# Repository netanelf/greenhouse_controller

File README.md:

# greenhouse_controller

## Executive Summary

An edge-based IoT monitoring and irrigation control system designed for long-term autonomous operation. 
The system integrates custom hardware (Raspberry Pi HAT), environmental sensors, actuator control (relays/SSR), event-driven automation logic, 
and a web-based monitoring interface built with Django. 
Deployed in real-world conditions and operated continuously for multiple years, enabling reliable unattended autonomous operation.

## Introduction

This project was developed to explore the design of reliable edge-based automation systems combining custom hardware, embedded software, and a full-stack web interface. The system was deployed in a real greenhouse environment and operated continuously over multiple growing seasons.

## System Architecture

The system follows an edge-controller architecture:

Sensors → Custom HAT Board → Raspberry Pi (Edge Controller) → Django Backend → Web Interface

- Local sensing and actuation handled directly by the Raspberry Pi.
- Control logic executed locally (no cloud dependency).
- Web interface for monitoring, configuration, and manual override.
- SQLite-based data storage with lightweight retention strategy.
- Event-driven automation engine enables flexible rule-based control without modifying core application code.

## Key Engineering Decisions

- Used 74HC595 shift register to expand GPIO outputs efficiently.
- Designed custom PCB HAT for reliable sensor and actuator interfacing.
- Implemented database separation strategy to mitigate SD-card wear and improve long-term reliability.
- Implemented event-condition-action flow engine for flexible automation logic.
- Ensured safe driving of relays via transistor stages and current-limited LED indicators.

## Hardware & Sensor Integration Overview

The system interfaces with temperature, humidity, light, and water flow sensors, as well as relay-controlled irrigation outputs and a camera module for periodic image capture.

The custom HAT board provides electrical interfacing, signal conditioning, and output expansion.

The architecture was designed to run on a Raspberry Pi, using its IOs through a dedicated hat board that interfaces directly with sensors and relays.
Key hardware features:
1. A 74HC595A shift register was used to expand available digital outputs.
2. the board includes:
   1. Connector for external 5V power capable of supplying the board and/or the HAT (selectable via solder jumper)
   2. 4 outputs that can control a SSR/ Relay with connectors for an indicator LED (board includes a current limiting resistor)
   3. 4 outputs of raw digital pins from the shift register (no LED/ Driver/ protection)
   4. 4 connectors for I2C sensors, connectors include the communication pins (scl,sda) and a 3.3/4V supply selected with a soldered jumper
   5. 3 dedicated connectors for a "Maxim Integrated DS18B20" 1-wire thermometer
   6. 3 dedicated connectors for a "AM2302/DHT22" digital temperature and humidity sensor
   7. pins for interfacing with all the RPi GPIOs (40p connector)
   8. pads for the shift register, driving transistors, and passive components

The project was built using the Django python library that implements the backend and frontend.
Custom drivers were implemented where required; existing open-source drivers were integrated where appropriate.
for example:
1. Maxim Integrated DS18B20 thermometer
2. AM2302/DHT22 temperature and humidity sensor
3. generic water flow sensor (pulse per known amount of flow)
4. TSL2561 Lux sensor
5. generic digital input/output lines (can be used for level sensors etc.)
6. a camera driver (uses the RPi camera interface)
   
## hat board schematic and layout

## Control options

The system implements an event-condition-action automation model. 
Users can define scheduled events, conditional logic, and associated control actions through the web interface.

an example watering flow can be:
- at 8:00 of days 1,3,5:
	- turn ON relay A
	- wait 10 minutes
	- turn OFF relay A

another flow can be to save sensor images to a DB:
- every 5 minutes:
  - read sensor A, save value to DB
  - read sensor B, save value to DB
  - ...
 
## web UI

The Django-based web interface provides:

- Configuration of automation flows
- Real-time visualization of sensor data
- Current relay states and actuator status
- Latest captured camera image
- Manual override controls for direct actuation

The Django admin interface is used for advanced configuration and rule management.

## Lessons Learned

### Edge System Constraints
- SD-card wear and limited I/O throughput require careful database management.
	- Measurements exceeding a configured retention threshold are migrated from db.sqlite3 to backup.sqlite3 to limit database growth and reduce SD-card wear.
 	- backup.sqlite3 can be copied regularly to a strong computer
- Power stability is critical when driving inductive loads.

### System Design Insight
- Designing for maintainability and observability from the beginning significantly simplifies long-term operation and troubleshooting.

### Reliability
- Long-running systems require watchdog-like recovery strategies.
- Sensor drift and environmental exposure must be handled in software logic.

### Hardware–Software Integration
- Clear abstraction layers between hardware drivers and application logic simplify long-term maintenance.

## Potential Extensions
- Cloud integration for remote monitoring
- OTA update mechanism
- Containerized deployment model
- Centralized logging and metrics collection

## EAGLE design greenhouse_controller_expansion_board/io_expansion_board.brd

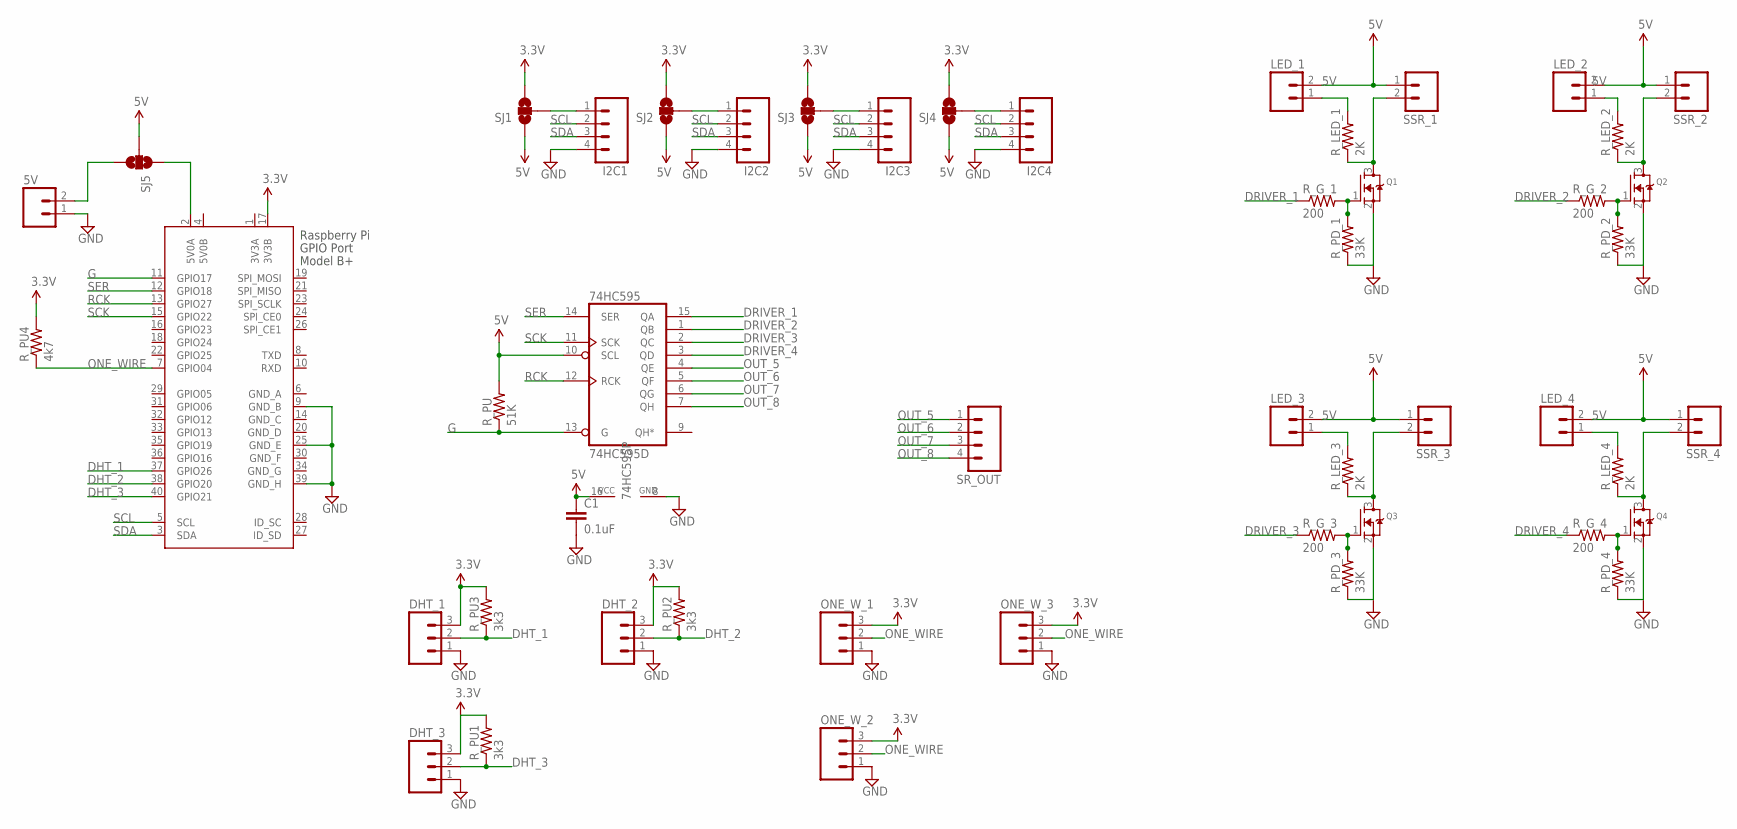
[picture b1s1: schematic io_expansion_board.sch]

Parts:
5V: M023.5MM; SCREWTERMINAL-3.5MM-2
74HC595: 74HC595D; SO16
C1: 0.1uF; 0603-CAP
DHT_1, DHT_2, DHT_3: M03POLAR; MOLEX-1X3
I2C1, I2C2, I2C3, I2C4: M04PTH; 1X04
LED_1, LED_2, LED_3, LED_4: M02PTH; 1X02
ONE_W_1, ONE_W_2, ONE_W_3: M03POLAR; MOLEX-1X3
Q1, Q2, Q3, Q4: MOSFET-NREFLOW; SOT23
R_G_1, R_G_2, R_G_3, R_G_4: 200; 0603-RES
R_LED_1, R_LED_2, R_LED_3, R_LED_4: 2K; 0603-RES
R_PD_1, R_PD_2, R_PD_3, R_PD_4: 33K; 0603-RES
R_PU: 51K; 0603-RES
R_PU1, R_PU2, R_PU3: 3k3; 0603-RES
R_PU4: 4k7; 0603-RES
SJ1, SJ2, SJ3, SJ4, SJ5: SOLDERJUMPER_2WAYS; SJ_3
SR_OUT: M04PTH; 1X04
SSR_1, SSR_2, SSR_3, SSR_4: M02PTH; 1X02
X2: RASPI_BOARD_B+#_HDC; RASPI_BOARD_B+HAT_DF_CF

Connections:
3.3V: DHT_1.3, DHT_2.3, DHT_3.3, ONE_W_1.3, ONE_W_2.3, ONE_W_3.3, R_PU1.2, R_PU2.2, R_PU3.2, R_PU4.2, SJ1.3, SJ2.3, SJ3.3, SJ4.3, X2.17 (3V3B)
3V3A: X2.1 (3V3A)
5V: 74HC595.10 (SCL), 74HC595.16 (VCC), C1.1, LED_1.2, LED_2.2, LED_3.2, LED_4.2, R_PU.2, SJ1.1, SJ2.1, SJ3.1, SJ4.1, SJ5.2, SSR_1.1, SSR_2.1, SSR_3.1, SSR_4.1
5V0B: X2.4 (5V0B)
DHT_1: DHT_1.2, R_PU3.1, X2.37 (GPIO26)
DHT_2: DHT_2.2, R_PU2.1, X2.38 (GPIO20)
DHT_3: DHT_3.2, R_PU1.1, X2.40 (GPIO21)
DRIVER_1: 74HC595.15 (QA), R_G_1.1
DRIVER_2: 74HC595.1 (QB), R_G_2.1
DRIVER_3: 74HC595.2 (QC), R_G_3.1
DRIVER_4: 74HC595.3 (QD), R_G_4.1
G: 74HC595.13 (G), R_PU.1, X2.11 (GPIO17)
GND: 5V.1, 74HC595.8 (GND), C1.2, DHT_1.1, DHT_2.1, DHT_3.1, I2C1.4 (GND), I2C2.4 (GND), I2C3.4 (GND), I2C4.4 (GND), ONE_W_1.1, ONE_W_2.1, ONE_W_3.1, Q1.2 (S), Q2.2 (S), Q3.2 (S), Q4.2 (S), R_PD_1.1, R_PD_2.1, R_PD_3.1, R_PD_4.1, X2.9 (GND_B), X2.25 (GND_E), X2.39 (GND_H)
GND_A: X2.6 (GND_A)
GND_C: X2.14 (GND_C)
GND_D: X2.20 (GND_D)
GND_F: X2.30 (GND_F)
GND_G: X2.34 (GND_G)
unnamed: Q2.1 (G), R_G_2.2, R_PD_2.2
unnamed: Q2.3 (D), R_LED_2.1, SSR_2.2
unnamed: LED_2.1, R_LED_2.2
unnamed: Q3.1 (G), R_G_3.2, R_PD_3.2
unnamed: Q1.1 (G), R_G_1.2, R_PD_1.2
unnamed: Q1.3 (D), R_LED_1.1, SSR_1.2
unnamed: LED_1.1, R_LED_1.2
unnamed: Q3.3 (D), R_LED_3.1, SSR_3.2
unnamed: LED_3.1, R_LED_3.2
unnamed: Q4.1 (G), R_G_4.2, R_PD_4.2
unnamed: Q4.3 (D), R_LED_4.1, SSR_4.2
unnamed: LED_4.1, R_LED_4.2
unnamed: I2C1.1 (SCL), SJ1.2
unnamed: I2C2.1 (SCL), SJ2.2
unnamed: I2C3.1 (SCL), SJ3.2
unnamed: I2C4.1 (SCL), SJ4.2
unnamed: SJ5.1, X2.2 (5V0A)
unnamed: 5V.2, SJ5.3
ONE_WIRE: ONE_W_1.2, ONE_W_2.2, ONE_W_3.2, R_PU4.1, X2.7 (GPIO04)
OUT_5: 74HC595.4 (QE), SR_OUT.1 (SCL)
OUT_6: 74HC595.5 (QF), SR_OUT.2 (SDA)
OUT_7: 74HC595.6 (QG), SR_OUT.3 (VCC)
OUT_8: 74HC595.7 (QH), SR_OUT.4 (GND)
RCK: 74HC595.12 (RCK), X2.13 (GPIO27)
SCK: 74HC595.11 (SCK), X2.15 (GPIO22)
SCL: I2C1.2 (SDA), I2C2.2 (SDA), I2C3.2 (SDA), I2C4.2 (SDA), X2.5 (SCL)
SDA: I2C1.3 (VCC), I2C2.3 (VCC), I2C3.3 (VCC), I2C4.3 (VCC), X2.3 (SDA)
SER: 74HC595.14 (SER), X2.12 (GPIO18)

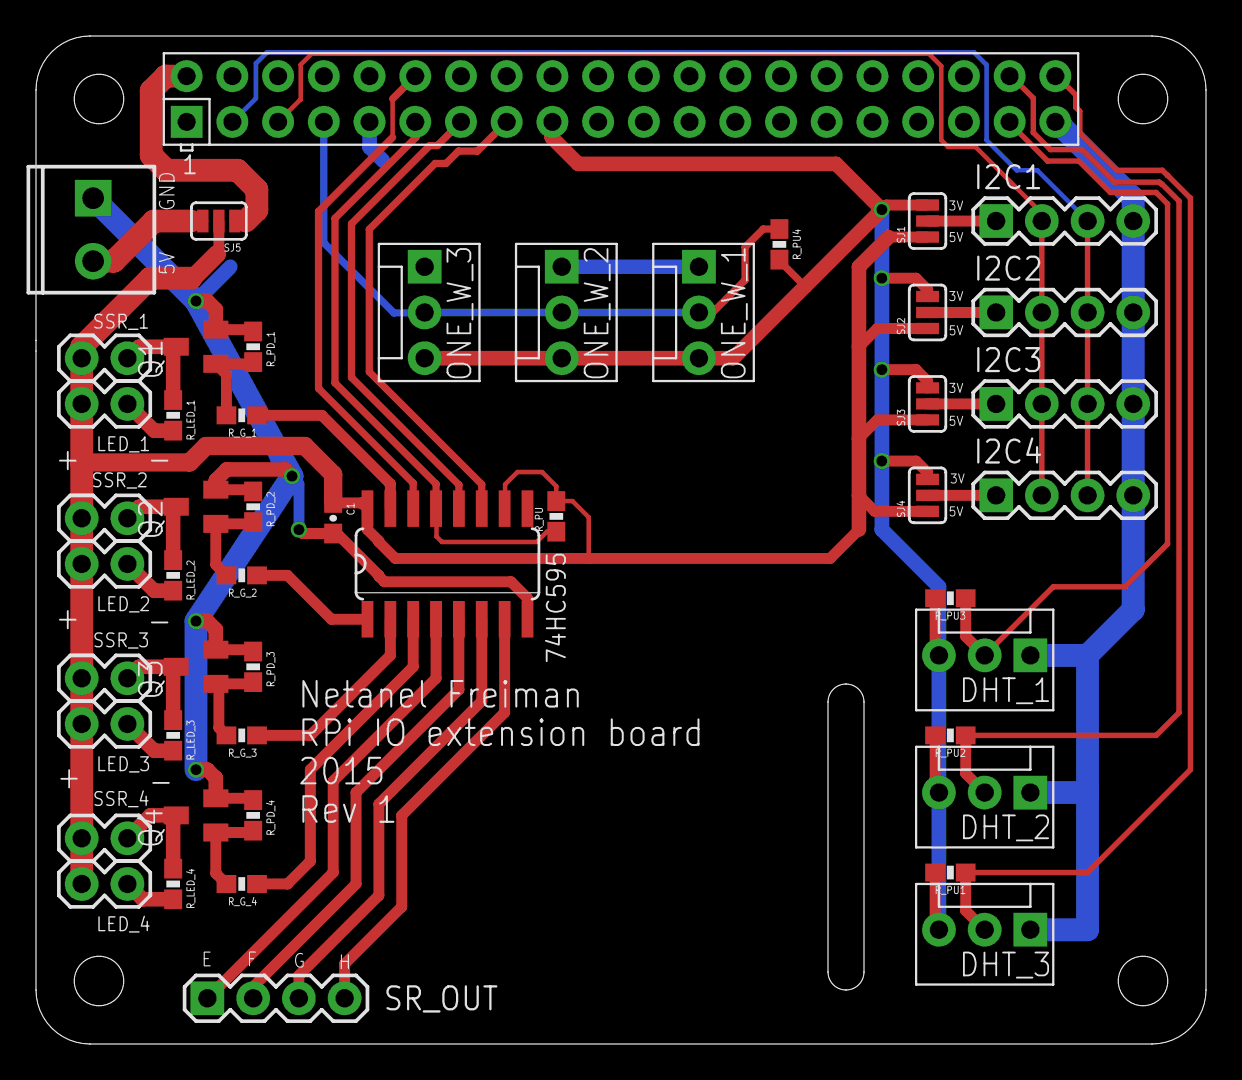
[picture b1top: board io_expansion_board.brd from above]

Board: 2 copper layers, 65.0 x 56.0 mm, 49 parts (0 on the bottom side), 39 nets.

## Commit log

2015-09-23 started project
2015-09-23 - added dht22 sensor controller - started 'brain' - controller object
    can run on PC: sensors can be emulated
2015-09-23 added data_sheet directory added logs directory
2015-09-28 - added web directory - started a django project (greenhouse_django_project) - started a django app (greenhouse app)
2015-09-29 some more arrangements of the library structure works in raspberry pi (server + brain)
2015-09-30 started to design web site
2015-10-01 changhed db to include date of measurement
2015-10-02 built relay controller in core. aterted to implement relays in web
2015-10-02 added windows batch run file
2015-10-02 - added linux run script - relay states can be changed from web client
2015-10-03 - created governors no govern relay on/off state (racurring and on off once a day)
2015-10-03 index page shows last read for every sensor, relay state and governors sensors and relays are refreshed automatically
2015-10-04 some changes from run in Rpi
2015-10-04 real relay controller debugging
2015-10-05 - added manual mode - added configuration table (currently only manual mode is read from there ) - updated population scripts
2015-10-05 tranclate pin number to GPIO number (in DHT22)
2015-10-05 relay controller change in Rpi
2015-10-05 fixed merge
2015-10-05 Rpi changes
2015-10-05 added bootstrap-toggle
2015-10-05 DHT22 improvements
2015-10-05 some refractoring
2015-10-06 wrote sr_controller (shift register), need to be checked on hardware
2015-10-10 wrote lcd drivers
2015-10-10 checked sr_driver with real HW, some minor bugs, everything works now
2015-10-10 some changes for simulation mode running
2015-10-10 changes from running on the raspberry pi, shift registar + relays work
2015-10-13 - changer sensor reading to synchronous reading. - implemented sensor reading output to lcd - changed html "probing" time to 5 [S]
2015-10-14 - retrieving of last measurements from db maid a lot more efficiently - stream file for downloading measurements - small indication on lcd for running core
2015-10-16 DHT 22 read only 3 times with smaller delay
2015-10-16 - changed number of retries and delay in DHT22 reading - added DS18B20 driver
2015-10-16 removed db from git
2015-10-16 - added DS18B20 controller
2015-10-16 - added DS18B20 kind, populate
2015-10-16 some changes in population script and model defines
2015-10-17 - created dht22 driver, this way temp + humidituy from same driver should be read once
2015-10-17 - lcd disconnecting/ removing should not crash the program
2015-10-17 - tlc2561 lux sensor added, not checked with HW yet
2015-10-17 fixed little/big endian bug in tsl2561 driver
2015-10-17 - tlc2561 lux sensor works - added 3.3V regulator datasheet
2015-10-19 started to implement graph showing from db
2015-10-19 timezone changed to 'browser'
2015-10-23 working on the graphs
2015-10-24 working on the graphs - adding previous days button works - save color per tag and do not swap - only fetch data when needed
2015-10-24 removed debug printing in vew. database TIMEOUT changed to 20 [S]
2015-10-24 - fix unwanted calling for data every time show_graph is pushed
2015-10-24 added date to tooltip, bug fix from run in Rpi
2015-11-03 invert relay modes in shift register
2015-12-05 ganged onn/off logic values fro ssr relays
2015-12-05 started creating readme for populations, added nice viewing of data from admin console
2015-12-05 debug logging in relay/ SR
2015-12-12 added run command to run server + core from one file (linux)
2015-12-18 removed unnecesary imports of GPIO, we run only in Rpi now
2015-12-18 change relays to work directly and not through SR
2016-01-13 wrote pcf8574_driver : not checked with HW yet
2016-01-15 added a .gotignore file to ignore pyc and log files
2016-01-16 - full support for simulate mode (HW lib import are handeled in __init__ conditionally ) - write into Measurements when a relay state is changed - add ControllerObject Model, Sensors and Relays inher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
2016-01-17 - added day/time widjet for graph selections (for now, everytime the whole data is sent and we do not save the overlapping data in the client...)
2016-01-23 - changing configuration to work with IO extension board
2016-01-29 added anable pin in shift register driver
2016-01-29 some changes to work with new IO board
2016-08-01 - stop using Adafruit i2c, depricated
2016-09-03 try to use Adafruit TSL driver +I2C
2016-09-03 - lux sensor working (with Adafruit drivers) fixed bug in 1-wire temp sensor driver
2016-09-05 minor updates for real setup
2016-09-05 minor updates for real setup 2
2016-09-09 - lcd alive should not print errors if we didnt initialize it - added index on time of measurement
2016-09-10 1. feature support on/off governors from one day to next (6PM -- 6AM (next day)) 2. refractor configurations --> configuration 3. tsl2561 import HW only if not simulated
2016-09-10 1.(self.lcd is not None) doesnt work ...
2016-09-10 safe timestamp of measure (no need gor conversion, takes more place - but quicker)
2016-11-11 try to use django-dbbackup
2016-11-14 back to home made backupper - move most records to other db
2016-11-14 - updated readme - db_backup: keep_parents not supported in django 1.7.7 (on Rpi) - support for None returning from sensor (if read didn't succeed)
2016-11-19 DbMover: from time to time, move the backupdB to a remote folder (this folder will be the server for viewing graphs)
2017-02-20 changes from rpi
2017-02-20 changes from pc
2017-02-20 moved to RotatingFileHandler
2017-02-21 some tweeks from running
2017-02-26 1. fixed on_off TimeGoverner 2. moved init_logging to utils 3. started to use logging inside django web classes 4. started to implement saving of history data in small cache inside sensor controllers
2017-02-26 fixed config to real config
2017-03-04 added history to other sensors
2017-03-06 wrote image_capture: capture images through raspistill
2017-03-11 insert helper threads into main one. controll image captures by lux reading
2017-03-11 logging configuration and printing changes
2017-03-11 fixes
2017-03-15 if some sensor failed reading, sensor_reading = None and we crash the brain thread
2017-03-15 ip fix
2017-03-17 added keepAlive: - avery module can register/ update keepalive through: register_keep_alive(name) and update_keep_alive(name) - ui shows KA time and state (60s = dead)
2017-04-07 logger.exception try
2017-04-17 wrote a failure_manager module
2017-04-17 restart command fixed
2017-11-17 Fixes
    - README
    - Changed the IP so it works on every computer.
    - ALLOWED_HOSTS which seems to be required for Django >1.7.7
2019-08-16 some minor updates for running on current django version
2019-08-20 some updates from pi
2019-08-22 updated recurring timegoverner to work with Timedelta
2019-08-23 log server timing for understanding db locks on raspberry pi
2019-08-24 added 'inverted' configuration for relays
2019-08-28 added try in main brain loop
2019-09-03 relay / sensors/ keepalive/ configuration timing were decoupled in brain loop
2019-10-09 added DigitalInputSensor graph minor fix
2019-10-09 no need to run eith sudo
2019-10-29 added timestamps embedded into pictures
2019-11-26 from rpi
2020-06-09 support for python 3
2020-06-13 implementing flow(event, condition, action): wip
2020-06-15 flow seems to be implemented in Model/ Admin starting to work on core side
2020-06-18 current measurements are saved/ in CurrentValue (updated - no history) historical measurements can be written to HistoryValue
2020-06-18 EventEveryDT tested to work
2020-06-21 minor (django 3)
2020-06-21 Update
    - Added an Email action.
    - Added separate integer/string configuration models.
    - Changed to a generic configuration dictionary in brain.
    - Fixed the ActionSetRelayState condition when creating actions objects.
2020-06-21 Forgot this
2020-06-22 Windows stuff
2020-06-22 Polymorphic working yey
    Adding polymorphic_list=True in a base polymorphic admin model allows to properly get child classes in the admin interface.
    I added it to the relevant classes and used __str__ to show nice names on the web.
    This is technically very unoptimized with regards to DB usage, but since it's used for things that probably won't pass the tens of objects all together, I doubt it matters. Citation needed :)
2020-06-26 minor: 1. remove event/ action Name property from code + populate script 2. fix graphs page
2020-06-26 updated populate_greenhouse_app_rpi_netanel.py to match current state of code
2020-06-26 from pi
2020-06-26 minor, for rpi
2020-06-27 manual mode, wip
2020-06-29 manual mode, relays controlling seems to work. changed relays view in main page (relays work now exactly like sensors)
2020-06-30 added action ActionCaptureImageAndSave
2020-06-30 added simulation capability to ActionCaptureImageAndSave
2020-07-04 added EventAtTimeTDays: fire at time t at certain days in the week
2020-07-04 DHT22: added caching in driver
2020-07-07 - added wait action - moved flow action running into separate threads (so we can use wait) - changed a bit the flow model - for easy selecting actions (even same ones again) and ensuring order of act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
2020-07-10 - image tab wip
2020-07-14 added conditions.py (with few initial conditions) added controller for flow sensor
2020-07-17 flow sensor configuration - rpi
2020-07-17 from rpi, flow sensor seems to work
2020-07-17 minor
2020-07-18 major (-: bug that data was never flushed... and we had many many updates to the DB
2020-07-21 run events (EventAtTimeTO, EventAtTimeTDaysO) only at time T or untill x seconds later (avoide rerunning events when program is restarted)
2020-07-25 wip, implementing JSON commands, sor flexible communication between program parts
2020-07-28 commands: a bit more structured. added CommandSetManualMode
2020-08-01 2 bugs fix, updated population script
2020-08-06 Added a flow view in the main page
2020-08-09 dht_22: check values are reasonable.
2020-08-14 added SHT drivers: flow works, actual communication to sensor was not tested... started to add units (for now target is better graphing)
2020-08-15 graphs: bunch graphs according to units population script: save all sensors to DB
2020-08-21 when reloading configuration - callback should be erased before adding again
2020-09-08 i2c tests
2020-09-08 sht i2c working on rpi
2020-12-24 implemented save picture button
2020-12-25 get camera output
2026-03-02 Add files via upload
    added images of the board schematics and layout

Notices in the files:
parts and their libraries:
SparkFun-Capacitors: Licensing: Creative Commons ShareAlike 4.0 International - https://creativecommons.org/licenses/by-sa/4.0
